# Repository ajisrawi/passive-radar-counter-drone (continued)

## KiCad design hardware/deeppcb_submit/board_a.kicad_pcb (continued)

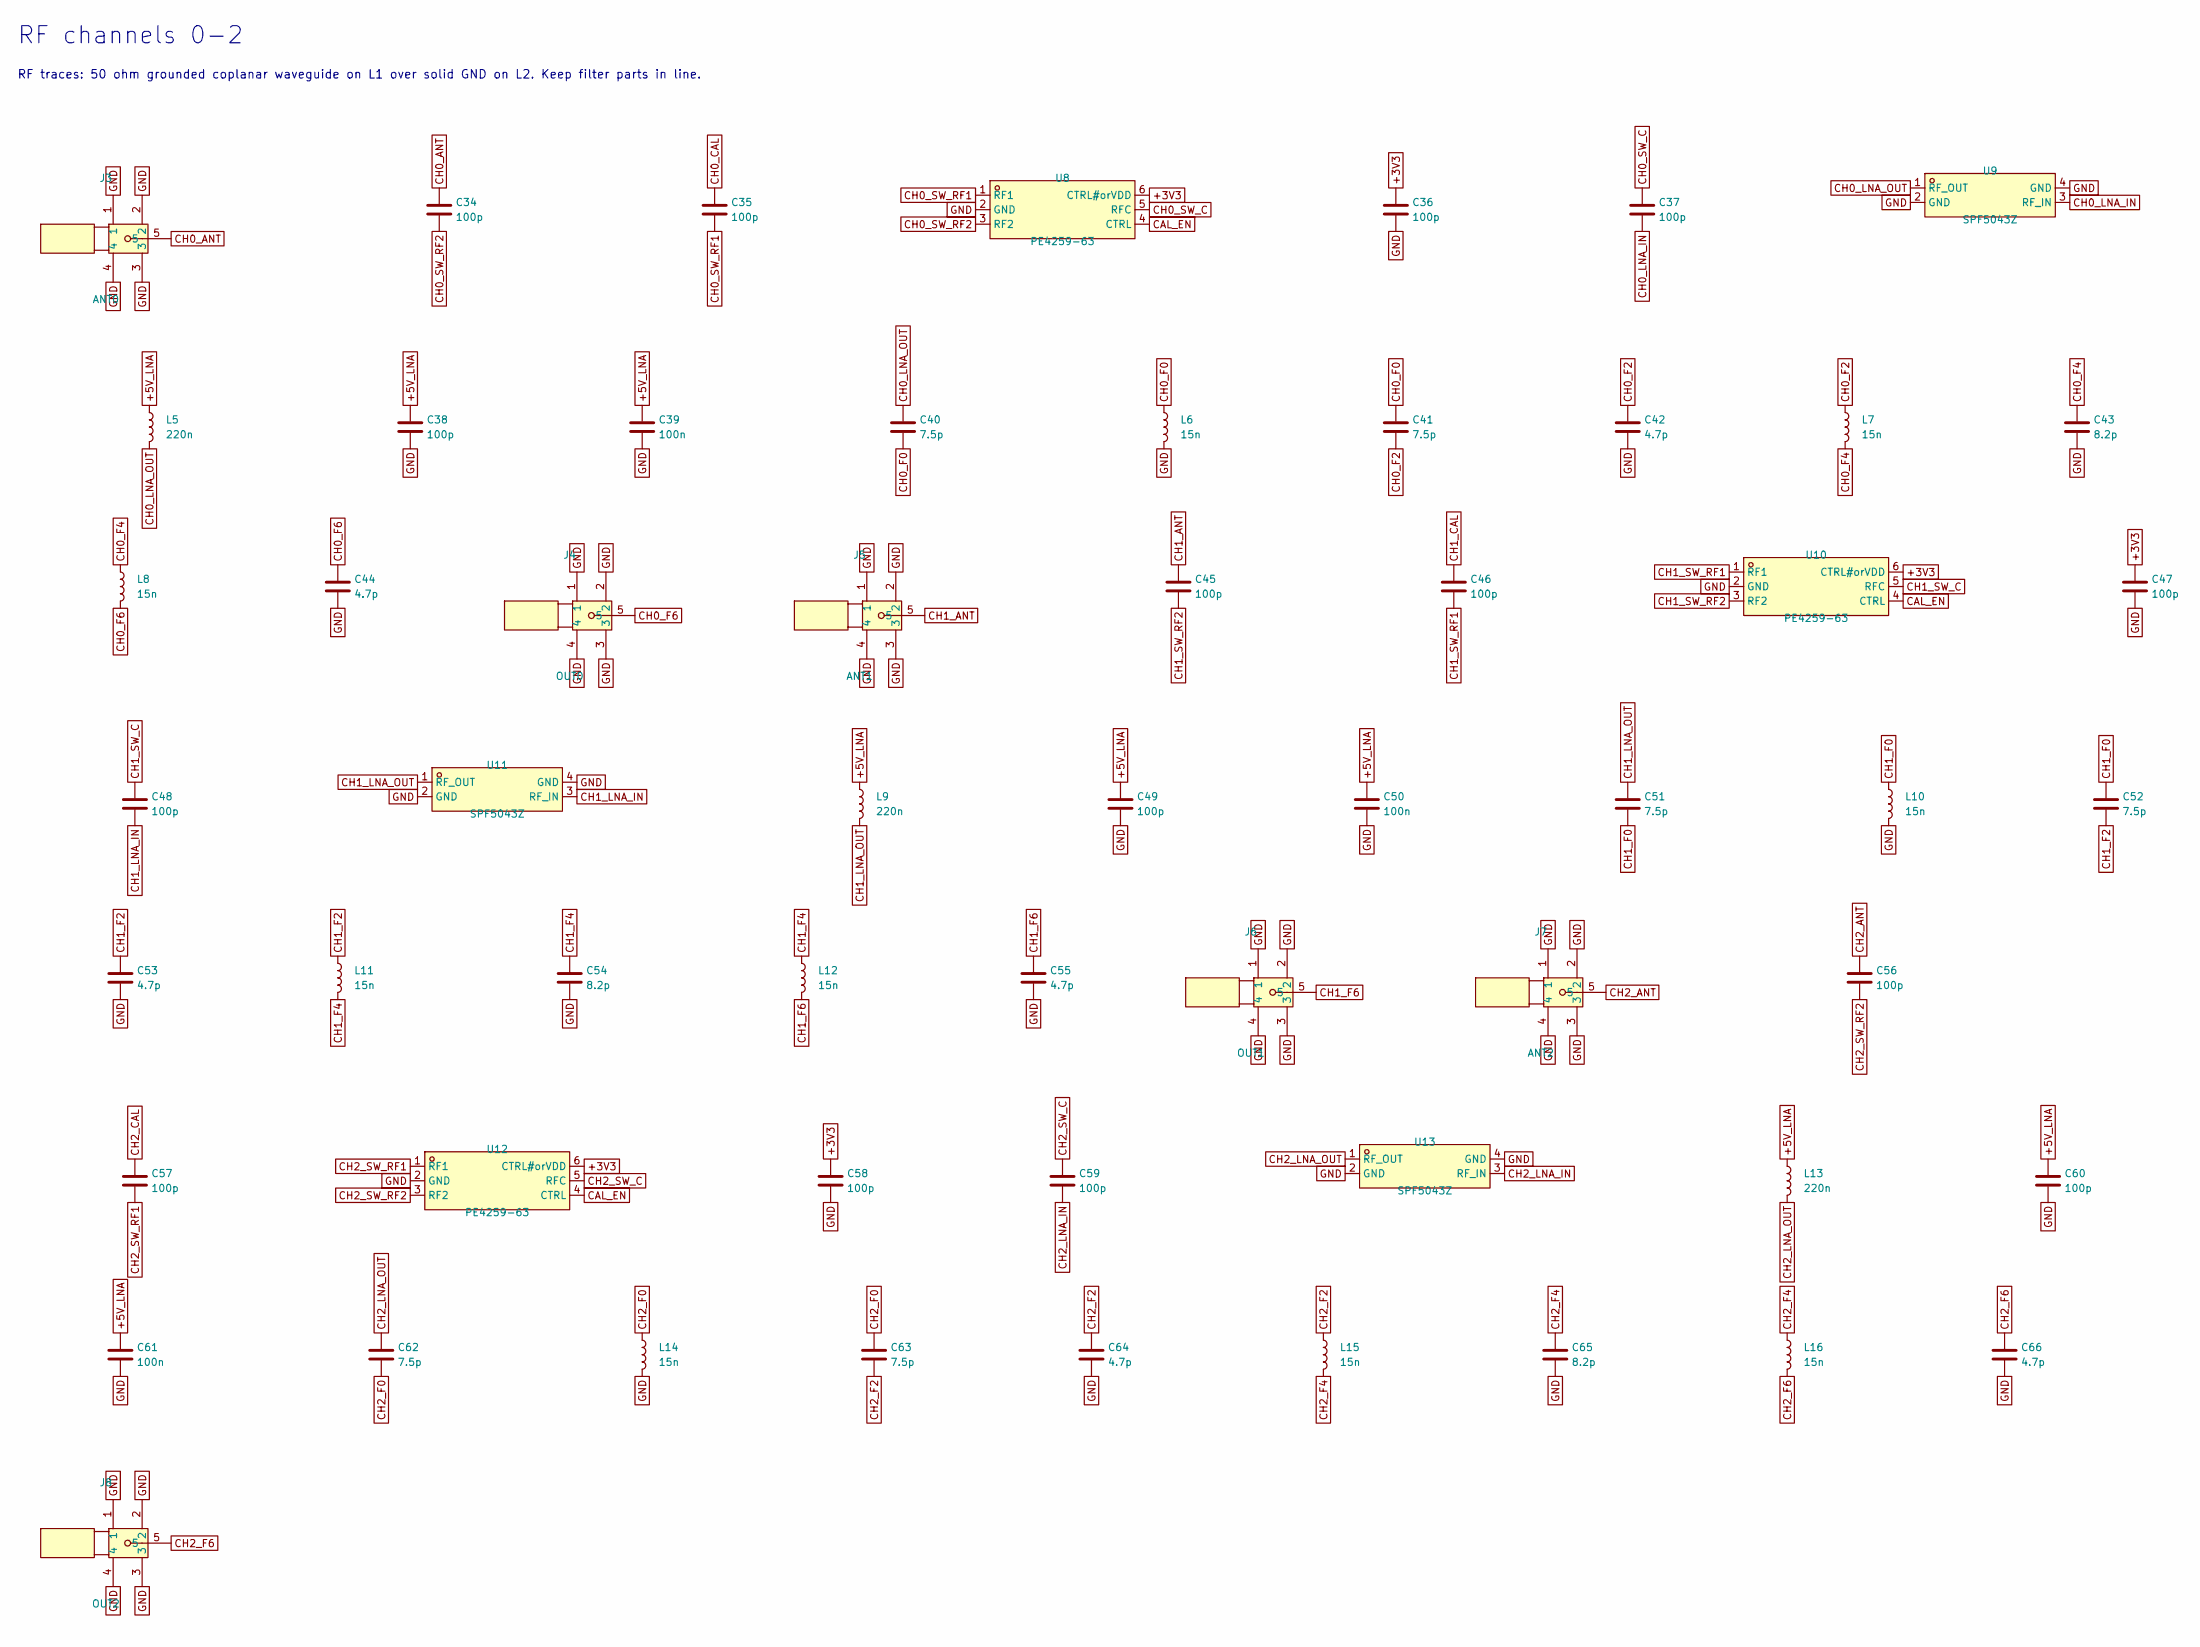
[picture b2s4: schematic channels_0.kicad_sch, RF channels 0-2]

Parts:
C34, C35, C36, C37, C38, C45, C46, C47, C48, C49, C56, C57, C58, C59, C60: 100p; C_0402_1005Metric
C39, C50, C61: 100n; C_0402_1005Metric; LCSC C1525
C40, C41, C51, C52, C62, C63: 7.5p; C_0402_1005Metric
C42, C44, C53, C55, C64, C66: 4.7p; C_0402_1005Metric
C43, C54, C65: 8.2p; C_0402_1005Metric
J3: ANT0; SMA-TH_BWSMA-KE-Z001; MPN BWSMA-KE-Z001; LCSC C496549
J4: OUT0; SMA-TH_BWSMA-KE-Z001; MPN BWSMA-KE-Z001; LCSC C496549
J5: ANT1; SMA-TH_BWSMA-KE-Z001; MPN BWSMA-KE-Z001; LCSC C496549
J6: OUT1; SMA-TH_BWSMA-KE-Z001; MPN BWSMA-KE-Z001; LCSC C496549
J7: ANT2; SMA-TH_BWSMA-KE-Z001; MPN BWSMA-KE-Z001; LCSC C496549
J8: OUT2; SMA-TH_BWSMA-KE-Z001; MPN BWSMA-KE-Z001; LCSC C496549
L5, L9, L13: 220n; L_0603_1608Metric
L6, L7, L8, L10, L11, L12, L14, L15, L16: 15n; L_0402_1005Metric
U8, U10, U12: PE4259-63; SC-70-6_L2.2-W1.3-P0.65-LS2.1-BL; MPN PE4259-63; LCSC C470892
U9, U11, U13: SPF5043Z; SOT343_L2.0-W1.3-P1.30-LS2.1-BL; MPN SPF5043Z; LCSC C470902

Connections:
+3V3: C36.1, C47.1, C58.1, U8.6 (CTRL#orVDD), U10.6 (CTRL#orVDD), U12.6 (CTRL#orVDD); also elsewhere on the board
+5V_LNA: C38.1, C39.1, C49.1, C50.1, C60.1, C61.1, L5.1, L9.1, L13.1; also elsewhere on the board
CAL_EN: U8.4 (CTRL), U10.4 (CTRL), U12.4 (CTRL); also elsewhere on the board
CH0_ANT: C34.1, J3.5
CH0_CAL: C35.1; also elsewhere on the board
CH0_F0: C40.2, C41.1, L6.1
CH0_F2: C41.2, C42.1, L7.1
CH0_F4: C43.1, L7.2, L8.1
CH0_F6: C44.1, J4.5, L8.2
CH0_LNA_IN: C37.2, U9.3 (RF_IN)
CH0_LNA_OUT: C40.1, L5.2, U9.1 (RF_OUT)
CH0_SW_C: C37.1, U8.5 (RFC)
CH0_SW_RF1: C35.2, U8.1 (RF1)
CH0_SW_RF2: C34.2, U8.3 (RF2)
CH1_ANT: C45.1, J5.5
CH1_CAL: C46.1; also elsewhere on the board
CH1_F0: C51.2, C52.1, L10.1
CH1_F2: C52.2, C53.1, L11.1
CH1_F4: C54.1, L11.2, L12.1
CH1_F6: C55.1, J6.5, L12.2
CH1_LNA_IN: C48.2, U11.3 (RF_IN)
CH1_LNA_OUT: C51.1, L9.2, U11.1 (RF_OUT)
CH1_SW_C: C48.1, U10.5 (RFC)
CH1_SW_RF1: C46.2, U10.1 (RF1)
CH1_SW_RF2: C45.2, U10.3 (RF2)
CH2_ANT: C56.1, J7.5
CH2_CAL: C57.1; also elsewhere on the board
CH2_F0: C62.2, C63.1, L14.1
CH2_F2: C63.2, C64.1, L15.1
CH2_F4: C65.1, L15.2, L16.1
CH2_F6: C66.1, J8.5, L16.2
CH2_LNA_IN: C59.2, U13.3 (RF_IN)
CH2_LNA_OUT: C62.1, L13.2, U13.1 (RF_OUT)
CH2_SW_C: C59.1, U12.5 (RFC)
CH2_SW_RF1: C57.2, U12.1 (RF1)
CH2_SW_RF2: C56.2, U12.3 (RF2)
GND: C36.2, C38.2, C39.2, C42.2, C43.2, C44.2, C47.2, C49.2, C50.2, C53.2, C54.2, C55.2, C58.2, C60.2, C61.2, C64.2, C65.2, C66.2, J3.1, J3.2, J3.3, J3.4, J4.1, J4.2, J4.3, J4.4, J5.1, J5.2, J5.3, J5.4, J6.1, J6.2, J6.3, J6.4, J7.1, J7.2, J7.3, J7.4, J8.1, J8.2, J8.3, J8.4, L6.2, L10.2, L14.2, U8.2 (GND), U9.2 (GND), U9.4 (GND), U10.2 (GND), U11.2 (GND), U11.4 (GND), U12.2 (GND), U13.2 (GND), U13.4 (GND); also elsewhere on the board

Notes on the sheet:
RF channels 0-2
RF traces: 50 ohm grounded coplanar waveguide on L1 over solid GND on L2. Keep filter parts in line.

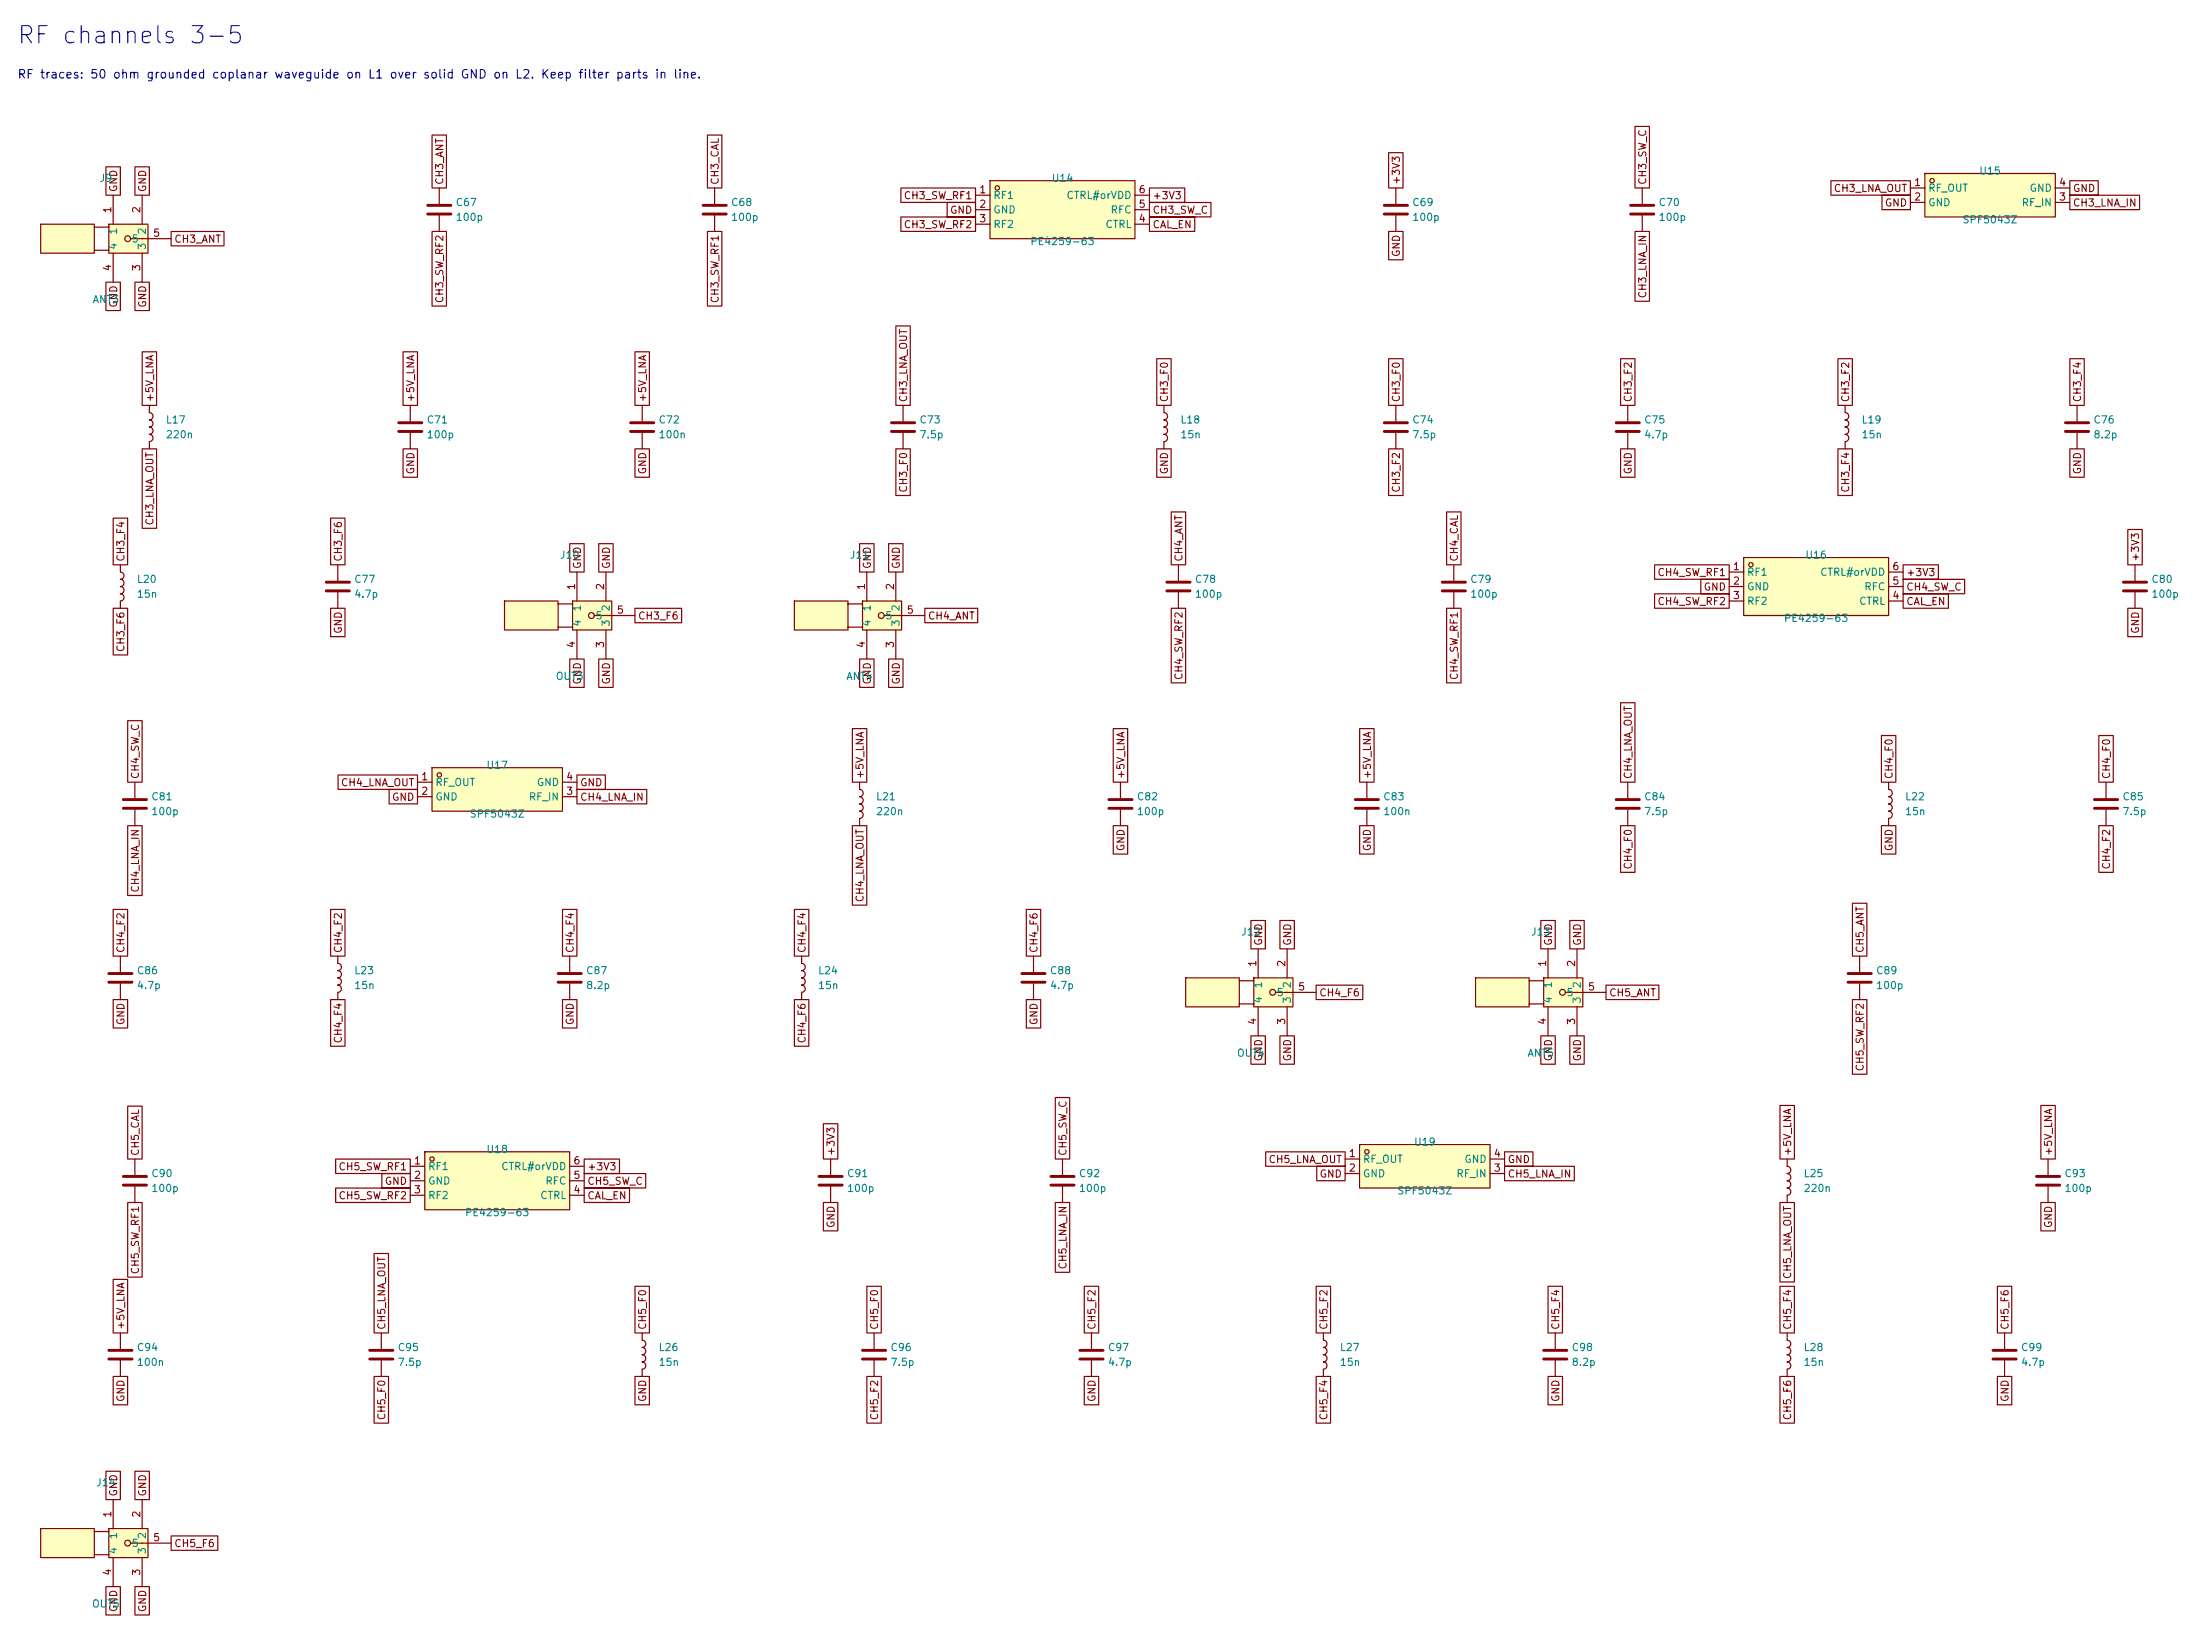
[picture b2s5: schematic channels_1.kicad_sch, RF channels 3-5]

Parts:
C67, C68, C69, C70, C71, C78, C79, C80, C81, C82, C89, C90, C91, C92, C93: 100p; C_0402_1005Metric
C72, C83, C94: 100n; C_0402_1005Metric; LCSC C1525
C73, C74, C84, C85, C95, C96: 7.5p; C_0402_1005Metric
C75, C77, C86, C88, C97, C99: 4.7p; C_0402_1005Metric
C76, C87, C98: 8.2p; C_0402_1005Metric
J9: ANT3; SMA-TH_BWSMA-KE-Z001; MPN BWSMA-KE-Z001; LCSC C496549
J10: OUT3; SMA-TH_BWSMA-KE-Z001; MPN BWSMA-KE-Z001; LCSC C496549
J11: ANT4; SMA-TH_BWSMA-KE-Z001; MPN BWSMA-KE-Z001; LCSC C496549
J12: OUT4; SMA-TH_BWSMA-KE-Z001; MPN BWSMA-KE-Z001; LCSC C496549
J13: ANT5; SMA-TH_BWSMA-KE-Z001; MPN BWSMA-KE-Z001; LCSC C496549
J14: OUT5; SMA-TH_BWSMA-KE-Z001; MPN BWSMA-KE-Z001; LCSC C496549
L17, L21, L25: 220n; L_0603_1608Metric
L18, L19, L20, L22, L23, L24, L26, L27, L28: 15n; L_0402_1005Metric
U14, U16, U18: PE4259-63; SC-70-6_L2.2-W1.3-P0.65-LS2.1-BL; MPN PE4259-63; LCSC C470892
U15, U17, U19: SPF5043Z; SOT343_L2.0-W1.3-P1.30-LS2.1-BL; MPN SPF5043Z; LCSC C470902

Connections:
+3V3: C69.1, C80.1, C91.1, U14.6 (CTRL#orVDD), U16.6 (CTRL#orVDD), U18.6 (CTRL#orVDD); also elsewhere on the board
+5V_LNA: C71.1, C72.1, C82.1, C83.1, C93.1, C94.1, L17.1, L21.1, L25.1; also elsewhere on the board
CAL_EN: U14.4 (CTRL), U16.4 (CTRL), U18.4 (CTRL); also elsewhere on the board
CH3_ANT: C67.1, J9.5
CH3_CAL: C68.1; also elsewhere on the board
CH3_F0: C73.2, C74.1, L18.1
CH3_F2: C74.2, C75.1, L19.1
CH3_F4: C76.1, L19.2, L20.1
CH3_F6: C77.1, J10.5, L20.2
CH3_LNA_IN: C70.2, U15.3 (RF_IN)
CH3_LNA_OUT: C73.1, L17.2, U15.1 (RF_OUT)
CH3_SW_C: C70.1, U14.5 (RFC)
CH3_SW_RF1: C68.2, U14.1 (RF1)
CH3_SW_RF2: C67.2, U14.3 (RF2)
CH4_ANT: C78.1, J11.5
CH4_CAL: C79.1; also elsewhere on the board
CH4_F0: C84.2, C85.1, L22.1
CH4_F2: C85.2, C86.1, L23.1
CH4_F4: C87.1, L23.2, L24.1
CH4_F6: C88.1, J12.5, L24.2
CH4_LNA_IN: C81.2, U17.3 (RF_IN)
CH4_LNA_OUT: C84.1, L21.2, U17.1 (RF_OUT)
CH4_SW_C: C81.1, U16.5 (RFC)
CH4_SW_RF1: C79.2, U16.1 (RF1)
CH4_SW_RF2: C78.2, U16.3 (RF2)
CH5_ANT: C89.1, J13.5
CH5_CAL: C90.1; also elsewhere on the board
CH5_F0: C95.2, C96.1, L26.1
CH5_F2: C96.2, C97.1, L27.1
CH5_F4: C98.1, L27.2, L28.1
CH5_F6: C99.1, J14.5, L28.2
CH5_LNA_IN: C92.2, U19.3 (RF_IN)
CH5_LNA_OUT: C95.1, L25.2, U19.1 (RF_OUT)
CH5_SW_C: C92.1, U18.5 (RFC)
CH5_SW_RF1: C90.2, U18.1 (RF1)
CH5_SW_RF2: C89.2, U18.3 (RF2)
GND: C69.2, C71.2, C72.2, C75.2, C76.2, C77.2, C80.2, C82.2, C83.2, C86.2, C87.2, C88.2, C91.2, C93.2, C94.2, C97.2, C98.2, C99.2, J9.1, J9.2, J9.3, J9.4, J10.1, J10.2, J10.3, J10.4, J11.1, J11.2, J11.3, J11.4, J12.1, J12.2, J12.3, J12.4, J13.1, J13.2, J13.3, J13.4, J14.1, J14.2, J14.3, J14.4, L18.2, L22.2, L26.2, U14.2 (GND), U15.2 (GND), U15.4 (GND), U16.2 (GND), U17.2 (GND), U17.4 (GND), U18.2 (GND), U19.2 (GND), U19.4 (GND); also elsewhere on the board

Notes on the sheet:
RF channels 3-5
RF traces: 50 ohm grounded coplanar waveguide on L1 over solid GND on L2. Keep filter parts in line.

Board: 4 copper layers, 194 parts (0 on the bottom side), 98 nets, no tracks yet.

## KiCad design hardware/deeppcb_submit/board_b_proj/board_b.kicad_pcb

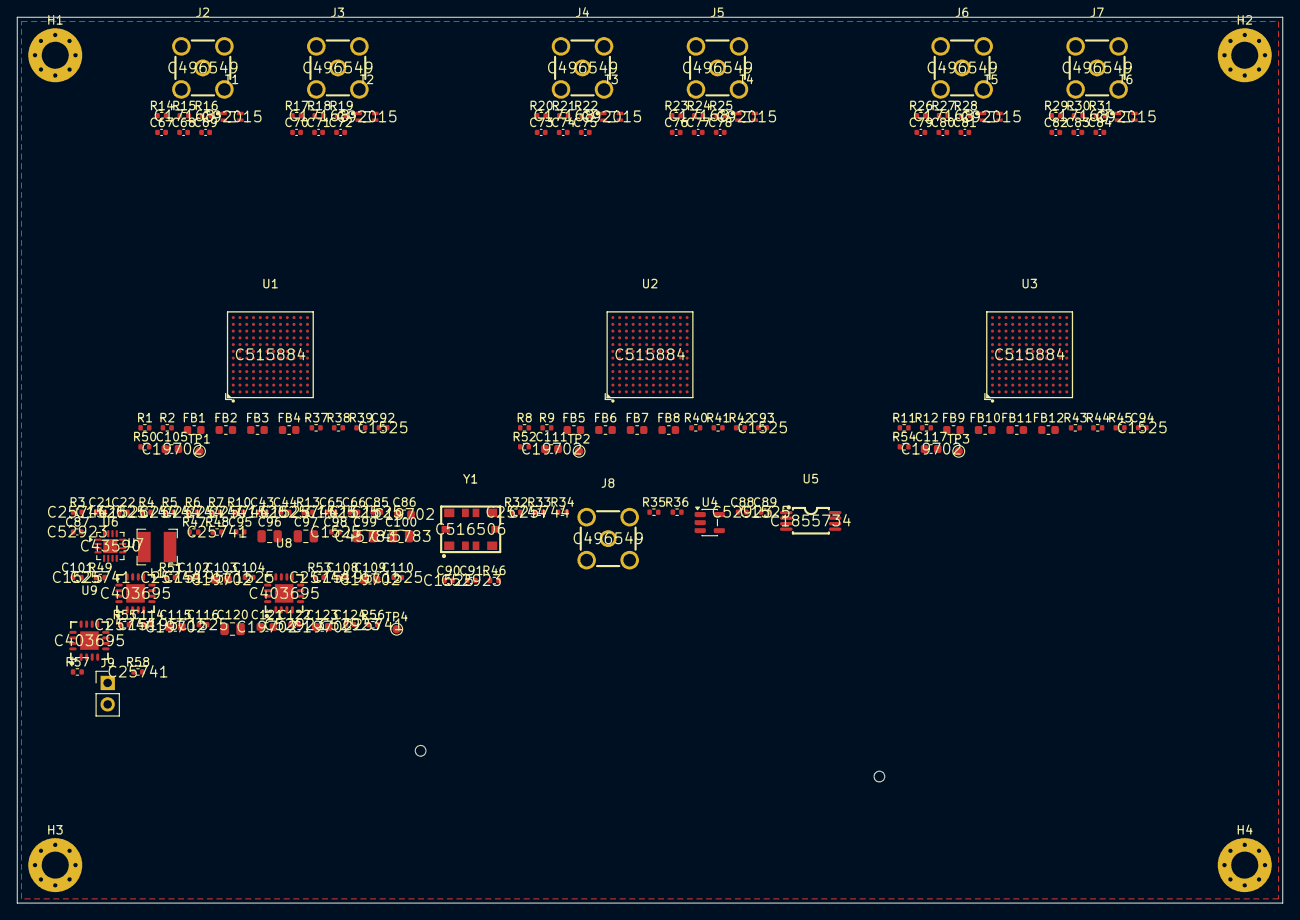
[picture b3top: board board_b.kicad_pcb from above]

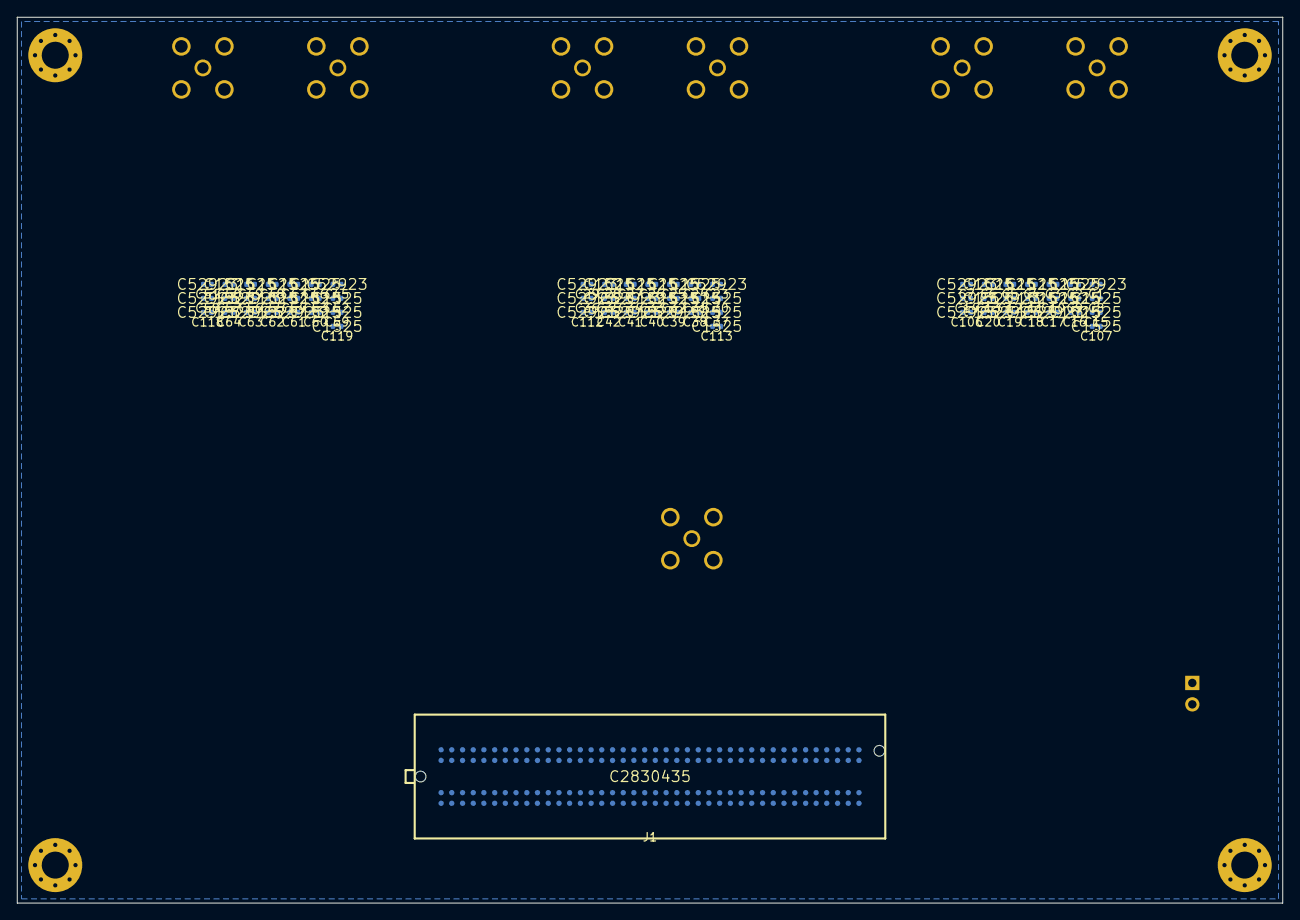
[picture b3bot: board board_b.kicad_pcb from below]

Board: 8 copper layers, 150.0 x 105.0 mm, 228 parts (67 on the bottom side), 166 nets, no tracks yet.

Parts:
C1, C7, C12, C14, C17, C19, C23, C29, C34, C36, C39, C41, C45, C51, C56, C58, C61, C63, C87, C88, C91, C106, C112, C118, C122, C124: 1u; C_0402_1005Metric
C2, C3, C4, C5, C6, C8, C9, C10, C11, C13, C15, C16, C18, C20, C21, C22, C24, C25, C26, C27, C28, C30, C31, C32, C33, C35, C37, C38, C40, C42, C43, C44, C46, C47, C48, C49, C50, C52, C53, C54, C55, C57, C59, C60, C62, C64, C65, C66, C85, C89, C90, C92, C93, C94, C98, C101, C104, C107, C110, C113, C116, C119: 100n; C_0402_1005Metric
C67, C68, C70, C71, C73, C74, C76, C77, C79, C80, C82, C83: 100p; C_0402_1005Metric
C69, C72, C75, C78, C81, C84: DNP; C_0402_1005Metric
C86, C103, C105, C109, C111, C115, C117, C121, C123: 10u; C_0603_1608Metric
C95: 3.3n; C_0402_1005Metric
C96, C97, C120: 10u; C_0805_2012Metric
C99, C100: 22u; C_0805_2012Metric
C102, C108, C114: 10n; C_0402_1005Metric
FB1, FB2, FB3, FB4, FB5, FB6, FB7, FB8, FB9, FB10, FB11, FB12: 600R@100MHz; L_0603_1608Metric
H1, H2, H3, H4: M3; MountingHole_3.2mm_M3_Pad_Via
J1: FMC LPC (mezzanine); FPC_SMD_ASP-134604-01
J2: RF_IN0; SMA-TH_BWSMA-KE-Z001
J3: RF_IN1; SMA-TH_BWSMA-KE-Z001
J4: RF_IN2; SMA-TH_BWSMA-KE-Z001
J5: RF_IN3; SMA-TH_BWSMA-KE-Z001
J6: RF_IN4; SMA-TH_BWSMA-KE-Z001
J7: RF_IN5; SMA-TH_BWSMA-KE-Z001
J8: EXT_REF; SMA-TH_BWSMA-KE-Z001
J9: CAL_EN to board A; PinHeader_1x02_P2.54mm_Vertical
L1: 2.2u; L_Bourns-SRN4018
R1, R8, R11: 14.3k; R_0402_1005Metric
R2, R9, R12: 22; R_0402_1005Metric
R3, R4, R5, R6, R7, R10, R13, R32, R33, R51, R53, R55: 10k; R_0402_1005Metric
R14, R16, R17, R19, R20, R22, R23, R25, R26, R28, R29, R31, R35: DNP; R_0402_1005Metric
R15, R18, R21, R24, R27, R30: 0; R_0402_1005Metric
R34: 470; R_0402_1005Metric
R36: 1.5k; R_0402_1005Metric
R37, R40, R43, R46, R57: 33; R_0402_1005Metric
R38, R41, R44: 120; R_0402_1005Metric
R39, R42, R45: 100; R_0402_1005Metric
R47: 125k; R_0402_1005Metric
R48, R49, R56, R58: 100k; R_0402_1005Metric
R50, R52, R54: 16k; R_0402_1005Metric
T1, T2, T3, T4, T5, T6: ATB2012-50011; XFMR-SMD_ATB2012-50011-T000
TP1: AD1_1V3; TestPoint_Pad_D1.0mm
TP2: AD2_1V3; TestPoint_Pad_D1.0mm
TP3: AD3_1V3; TestPoint_Pad_D1.0mm
TP4: +1V8; TestPoint_Pad_D1.0mm
U1, U2, U3: AD9361BBCZ; CSPBGA-144_L10.0-W10.0-R12-C12-P0.80-BL
U4: TLV75525PDBVR; SOT-23-5
U5: LMK1C1104PWR; TSSOP-8_L4.4-W3.0-P0.65-LS6.4-TL
U6: TPS62130RGTR; VQFN-16-1EP_3x3mm_P0.5mm_EP1.68x1.68mm
U7, U8, U9: ADP1755ACPZ-R7; LFCSP-16_L4.0-W4.0-P0.65-BL-EP2.2
Y1: 40MHz TCXO 0.5ppm; OSC-SMD_10P-L7.0-W5.0-BL

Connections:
+1V8: C99.1, C100.1, C101.1, C103.1, C104.1, C109.1, C110.1, C115.1, C116.1, L1.2, R47.1, R49.2, TP4.1, U6.14, U7.1, U7.2, U7.3, U7.15, U7.16, U8.1, U8.2, U8.3, U8.15, U8.16, U9.1, U9.2, U9.3, U9.15, U9.16
+2V5_CLK: C88.1, C89.1, C90.1, C91.1, U4.5, U5.2, U5.6
+3V3: C22.1, C44.1, C66.1, C85.1, C86.1, C87.1, C123.1, C124.1, J1.C39, J1.D36, J1.D38, J1.D40, R32.1, U1.B8, U2.B8, U3.B8, U4.1, U4.3, Y1.4
+12V_FMC: C96.1, C97.1, C98.1, C120.1, J1.C35, J1.C37, U6.10, U6.11, U6.12
AD1_1V3: C105.1, C106.1, C107.1, FB1.1, FB2.1, FB3.1, FB4.1, R50.1, TP1.1, U7.10, U7.11, U7.12, U7.13, U7.14
AD1_1V3_BB: C12.1, C13.1, FB3.2, U1.K4
AD1_1V3_DIG: C14.1, C15.1, C16.1, FB4.2, U1.F12
AD1_1V3_RF: C1.1, C2.1, C3.1, C4.1, C5.1, C6.1, FB1.2, U1.B9, U1.D2, U1.D3, U1.E2, U1.E3
AD1_1V3_SYN: C7.1, C8.1, C9.1, C10.1, C11.1, FB2.2, U1.B10, U1.F2, U1.J3, U1.K3
AD1_CK_A: R37.2, R38.1
AD1_CK_B: C92.1, R38.2, R39.1
AD1_DCLK_N: J1.G07, U1.H11
AD1_DCLK_P: J1.G06, U1.G11
AD1_FBCLK_N: J1.D15, U1.G10
AD1_FBCLK_P: J1.D14, U1.F10
AD1_FRAME_N: J1.H08, U1.G7
AD1_FRAME_P: J1.H07, U1.G8
AD1_RBIAS: R1.1, U1.L4
AD1_RXD0_N: J1.G10, U1.K11
AD1_RXD0_P: J1.G09, U1.J12
AD1_RXD1_N: J1.H11, U1.K10
AD1_RXD1_P: J1.H10, U1.J11
AD1_RXD2_N: J1.D12, U1.K9
AD1_RXD2_P: J1.D11, U1.J10
AD1_RXD3_N: J1.C11, U1.K8
AD1_RXD3_P: J1.C10, U1.J9
AD1_RXD4_N: J1.H14, U1.K7
AD1_RXD4_P: J1.H13, U1.J8
AD1_RXD5_N: J1.G13, U1.J7
AD1_RXD5_P: J1.G12, U1.H8
AD1_RXVCO_1V1: C17.1, C18.1, U1.G2, U1.G3
AD1_SYNC: R2.2, U1.H5
AD1_TXVCO_1V1: C19.1, C20.1, U1.A11, U1.B11
AD1_XTALN: C92.2, U1.M12
AD2_1V3: C111.1, C112.1, C113.1, FB5.1, FB6.1, FB7.1, FB8.1, R52.1, TP2.1, U8.10, U8.11, U8.12, U8.13, U8.14
AD2_1V3_BB: C34.1, C35.1, FB7.2, U2.K4
AD2_1V3_DIG: C36.1, C37.1, C38.1, FB8.2, U2.F12
AD2_1V3_RF: C23.1, C24.1, C25.1, C26.1, C27.1, C28.1, FB5.2, U2.B9, U2.D2, U2.D3, U2.E2, U2.E3
AD2_1V3_SYN: C29.1, C30.1, C31.1, C32.1, C33.1, FB6.2, U2.B10, U2.F2, U2.J3, U2.K3
AD2_CK_A: R40.2, R41.1
AD2_CK_B: C93.1, R41.2, R42.1
AD2_DCLK_N: J1.D09, U2.H11
AD2_DCLK_P: J1.D08, U2.G11
AD2_FBCLK_N: J1.H23, U2.G10
AD2_FBCLK_P: J1.H22, U2.F10
AD2_FRAME_N: J1.C15, U2.G7
AD2_FRAME_P: J1.C14, U2.G8
AD2_RBIAS: R8.1, U2.L4
AD2_RXD0_N: J1.H17, U2.K11
AD2_RXD0_P: J1.H16, U2.J12
AD2_RXD1_N: J1.G16, U2.K10
AD2_RXD1_P: J1.G15, U2.J11
AD2_RXD2_N: J1.D18, U2.K9
AD2_RXD2_P: J1.D17, U2.J10
AD2_RXD3_N: J1.C19, U2.K8
AD2_RXD3_P: J1.C18, U2.J9
AD2_RXD4_N: J1.H20, U2.K7
AD2_RXD4_P: J1.H19, U2.J8
AD2_RXD5_N: J1.G19, U2.J7
AD2_RXD5_P: J1.G18, U2.H8
AD2_RXVCO_1V1: C39.1, C40.1, U2.G2, U2.G3
AD2_SYNC: R9.2, U2.H5
AD2_TXVCO_1V1: C41.1, C42.1, U2.A11, U2.B11
AD2_XTALN: C93.2, U2.M12
AD3_1V3: C117.1, C118.1, C119.1, FB9.1, FB10.1, FB11.1, FB12.1, R54.1, TP3.1, U9.10, U9.11, U9.12, U9.13, U9.14
AD3_1V3_BB: C56.1, C57.1, FB11.2, U3.K4
AD3_1V3_DIG: C58.1, C59.1, C60.1, FB12.2, U3.F12
AD3_1V3_RF: C45.1, C46.1, C47.1, C48.1, C49.1, C50.1, FB9.2, U3.B9, U3.D2, U3.D3, U3.E2, U3.E3
AD3_1V3_SYN: C51.1, C52.1, C53.1, C54.1, C55.1, FB10.2, U3.B10, U3.F2, U3.J3, U3.K3
AD3_CK_A: R43.2, R44.1
AD3_CK_B: C94.1, R44.2, R45.1
AD3_DCLK_N: J1.D21, U3.H11
AD3_DCLK_P: J1.D20, U3.G11
AD3_FBCLK_N: J1.D27, U3.G10
AD3_FBCLK_P: J1.D26, U3.F10
AD3_FRAME_N: J1.C23, U3.G7
AD3_FRAME_P: J1.C22, U3.G8
AD3_RBIAS: R11.1, U3.L4
AD3_RXD0_N: J1.G22, U3.K11
AD3_RXD0_P: J1.G21, U3.J12
AD3_RXD1_N: J1.H26, U3.K10
AD3_RXD1_P: J1.H25, U3.J11
AD3_RXD2_N: J1.G25, U3.K9
AD3_RXD2_P: J1.G24, U3.J10
AD3_RXD3_N: J1.D24, U3.K8
AD3_RXD3_P: J1.D23, U3.J9
AD3_RXD4_N: J1.H29, U3.K7
AD3_RXD4_P: J1.H28, U3.J8
AD3_RXD5_N: J1.G28, U3.J7
AD3_RXD5_P: J1.G27, U3.H8
AD3_RXVCO_1V1: C61.1, C62.1, U3.G2, U3.G3
AD3_SYNC: R12.2, U3.H5
AD3_TXVCO_1V1: C63.1, C64.1, U3.A11, U3.B11
AD3_XTALN: C94.2, U3.M12
AD_ENABLE: J1.H35, R6.1, U1.G6, U2.G6, U3.G6
AD_EN_AGC: J1.H38, R5.1, U1.G5, U2.G5, U3.G5
AD_RESETB: J1.H34, R4.1, U1.K5, U2.K5, U3.K5
AD_SYNC_IN: J1.G34, R2.1, R9.1, R12.1
AD_TXNRX: J1.G33, R7.1, U1.H4, U2.H4, U3.H4
BUCK1V8_FB: R47.2, R48.1, U6.5
BUCK1V8_SS: C95.1, U6.9
BUCK1V8_SW: L1.1, U6.1, U6.2, U6.3
CAL_EN: J9.1, R57.2, R58.1
CAL_EN_FPGA: J1.H37, R57.1
CH0_BAL: R15.2, R16.1, T1.1
CH0_BN: C68.1, T1.3
CH0_BP: C67.1, T1.4
CH0_IN: J2.5, R14.1, R15.1
CH0_RXN: C68.2, C69.2, U1.M2
CH0_RXP: C67.2, C69.1, U1.M1
CH1_BAL: R18.2, R19.1, T2.1
CH1_BN: C71.1, T2.3
CH1_BP: C70.1, T2.4
CH1_IN: J3.5, R17.1, R18.1
CH1_RXN: C71.2, C72.2, U1.A1
CH1_RXP: C70.2, C72.1, U1.A2
CH2_BAL: R21.2, R22.1, T3.1
CH2_BN: C74.1, T3.3
CH2_BP: C73.1, T3.4
CH2_IN: J4.5, R20.1, R21.1
CH2_RXN: C74.2, C75.2, U2.M2
CH2_RXP: C73.2, C75.1, U2.M1
CH3_BAL: R24.2, R25.1, T4.1
CH3_BN: C77.1, T4.3
CH3_BP: C76.1, T4.4
CH3_IN: J5.5, R23.1, R24.1
CH3_RXN: C77.2, C78.2, U2.A1
CH3_RXP: C76.2, C78.1, U2.A2
CH4_BAL: R27.2, R28.1, T5.1
CH4_BN: C80.1, T5.3
CH4_BP: C79.1, T5.4
CH4_IN: J6.5, R26.1, R27.1
CH4_RXN: C80.2, C81.2, U3.M2
CH4_RXP: C79.2, C81.1, U3.M1
CH5_BAL: R30.2, R31.1, T6.1
CH5_BN: C83.1, T6.3
CH5_BP: C82.1, T6.4
CH5_IN: J7.5, R29.1, R30.1
CH5_RXN: C83.2, C84.2, U3.A1
CH5_RXP: C82.2, C84.1, U3.A2
CLK_Y0: R37.1, U5.3
CLK_Y1: R40.1, U5.8
CLK_Y2: R43.1, U5.5
CLK_Y3: R46.1, U5.7
EXT_REF: J8.5, R35.1
FMC_TDI_TDO: J1.D30, J1.D31
FPGA_REFCLK: J1.H04, R46.2
GND: C1.2, C2.2, C3.2, C4.2, C5.2, C6.2, C7.2, C8.2, C9.2, C10.2, C11.2, C12.2, C13.2, C14.2, C15.2, C16.2, C17.2, C18.2, C19.2, C20.2, C21.2, C22.2, C23.2, C24.2, C25.2, C26.2, C27.2, C28.2, C29.2, C30.2, C31.2, C32.2, C33.2, C34.2, C35.2, C36.2, C37.2, C38.2, C39.2, C40.2, C41.2, C42.2, C43.2, C44.2, C45.2, C46.2, C47.2, C48.2, C49.2, C50.2, C51.2, C52.2, C53.2, C54.2, C55.2, C56.2, C57.2, C58.2, C59.2, C60.2, C61.2, C62.2, C63.2, C64.2, C65.2, C66.2, C85.2, C86.2, C87.2, C88.2, C89.2, C90.2, C91.2, C95.2, C96.2, C97.2, C98.2, C99.2, C100.2, C101.2, C102.2, C103.2, C104.2, C105.2, C106.2, C107.2, C108.2, C109.2, C110.2, C111.2, C112.2, C113.2, C114.2, C115.2, C116.2, C117.2, C118.2, C119.2, C120.2, C121.2, C122.2, C123.2, C124.2, H1.1, H2.1, H3.1, H4.1, J1.C01, J1.C04, J1.C05, J1.C08, J1.C09, J1.C12, J1.C13, J1.C16, J1.C17, J1.C20, J1.C21, J1.C24, J1.C25, J1.C28, J1.C29, J1.C32, J1.C33, J1.C36, J1.C38, J1.C40, J1.D02, J1.D03, J1.D06, J1.D07, J1.D10, J1.D13, J1.D16, J1.D19, J1.D22, J1.D25, J1.D28, J1.D37, J1.D39, J1.G01, J1.G04, J1.G05, J1.G08, J1.G11, J1.G14, J1.G17, J1.G20, J1.G23, J1.G26, J1.G29, J1.G32, J1.G35, J1.G38, J1.G40, J1.H02, J1.H03, J1.H06, J1.H09, J1.H12, J1.H15, J1.H18, J1.H21, J1.H24, J1.H27, J1.H30, J1.H33, J1.H36, J1.H39, J2.1, J2.2, J2.3, J2.4, J3.1, J3.2, J3.3, J3.4, J4.1, J4.2, J4.3, J4.4, J5.1, J5.2, J5.3, J5.4, J6.1, J6.2, J6.3, J6.4, J7.1, J7.2, J7.3, J7.4, J8.1, J8.2, J8.3, J8.4, J9.2, R1.2, R5.2, R6.2, R7.2, R8.2, R11.2, R14.2, R16.2, R17.2, R19.2, R20.2, R22.2, R23.2, R25.2, R26.2, R28.2, R29.2, R31.2, R33.2, R36.2, R39.2, R42.2, R45.2, R48.2, R51.2, R53.2, R55.2, R56.2, R58.2, T1.2, T2.2, T3.2, T4.2, T5.2, T6.2, U1.A4, U1.A6, U1.B1, U1.B2, U1.B12, U1.C2, U1.C4, U1.C5, U1.C6, U1.C7, U1.C8, U1.C9, U1.C10, U1.C11, U1.C12, U1.D5, U1.D6, U1.D12, U1.F3, U1.F7, U1.F9, U1.F11, U1.G12, U1.H2, U1.H3, U1.H6, U1.H7, U1.H10, U1.J2, U1.K2, U1.K12, U1.L2, U1.L3, U1.L7, U1.L8, U1.L9, U1.L10, U1.L11, U1.L12, U1.M4, U1.M6, U2.A4, U2.A6, U2.B1, U2.B2, U2.B12, U2.C2, U2.C4, U2.C5, U2.C6, U2.C7, U2.C8, U2.C9, U2.C10, U2.C11, U2.C12, U2.D5, U2.D6, U2.D12, U2.F3, U2.F7, U2.F9, U2.F11, U2.G12, U2.H2, U2.H3, U2.H6, U2.H7, U2.H10, U2.J2, U2.K2, U2.K12, U2.L2, U2.L3, U2.L7, U2.L8, U2.L9, U2.L10, U2.L11, U2.L12, U2.M4, U2.M6, U3.A4, U3.A6, U3.B1, U3.B2, U3.B12, U3.C2, U3.C4, U3.C5, U3.C6, U3.C7, U3.C8, U3.C9, U3.C10, U3.C11, U3.C12, U3.D5, U3.D6, U3.D12, U3.F3, U3.F7, U3.F9, U3.F11, U3.G12, U3.H2, U3.H3, U3.H6, U3.H7, U3.H10, U3.J2, U3.K2, U3.K12, U3.L2, U3.L3, U3.L7, U3.L8, U3.L9, U3.L10, U3.L11, U3.L12, U3.M4, U3.M6, U4.2, U5.4, U6.6, U6.7, U6.8, U6.15, U6.16, U6.17, U7.6, U7.17, U8.6, U8.17, U9.6, U9.17, Y1.2
LDO_AD1_ADJ: R50.2, R51.1, U7.9
LDO_AD1_SS: C102.1, U7.7
LDO_AD2_ADJ: R52.2, R53.1, U8.9
LDO_AD2_SS: C108.1, U8.7
LDO_AD3_ADJ: R54.2, R55.1, U9.9
LDO_AD3_SS: C114.1, U9.7
PG_1V8: R49.1, U6.4, U7.4, U8.4, U9.4
PG_C2M: J1.D01, R56.1, U6.13
REF_SEL: R34.2, R35.2, R36.1, U5.1
SPI_CLK: J1.C26, U1.J5, U2.J5, U3.J5
SPI_DI: J1.C27, U1.J4, U2.J4, U3.J4
SPI_DO: J1.H31, U1.L6, U2.L6, U3.L6
SPI_ENB1: J1.H32, R3.1, U1.K6
SPI_ENB2: J1.G30, R10.1, U2.K6
SPI_ENB3: J1.G31, R13.1, U3.K6
TCXO_OUT: R34.1, Y1.3
TCXO_VC: R32.2, R33.1, Y1.1
VADJ: C21.1, C43.1, C65.1, C121.1, C122.1, J1.G39, J1.H40, R3.2, R4.2, R10.2, R13.2, U1.H12, U2.H12, U3.H12
